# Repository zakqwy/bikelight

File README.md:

## bikelight

It's a blinky red light for the back of my bike helmet.

The circuit uses an ATtiny412 to control four red LEDs, along with a Microchip MCP73831 lipo charge controller for battery management and a micro-USB jack for charging.

The circuit is designed to be milled on a single sided chunk of FR1 using a 1/64" end mill. If you use [mods](mods.cba.mit.edu), the three layer *.svg files (holes, outline, and traces) are in the /pcb directory. After assembling and programming with [pyupdi](https://github.com/mraardvark/pyupdi) and an FTDI cable, I masked off the USB jack and slide switch and sprayed it with a few coats of clear varnish.

The pcb attaches using M3 hardware to two laser cut acetal clips, which then snap into [my helmet](https://www.bernhelmets.com/collections/bike/products/summer-watts?variant=13190223200315). If you have the same model, this will probably work for you too, otherwise you'll need to figure something else out. Laser cut files for these parts are in the /cad directory, intended to be cut from 2.5 mm acetal.

I used a 1200 mAH lipo battery since we had a few on hand; it's secured to the rear of the pcb using VHB tape. I snagged a JST PH off a spare Feather, but if you plan ahead you can buy the part [here](https://www.adafruit.com/product/1769). Note that lipo batteries are inherently dangerous, so don't build this circuit unless you're familiar with their quirks (and make sure to use one with a built-in protection circuit). Yes, if my helmet ever actually has to do its job, my head will likely catch fire.

bikelight! blink blink blink blink blink

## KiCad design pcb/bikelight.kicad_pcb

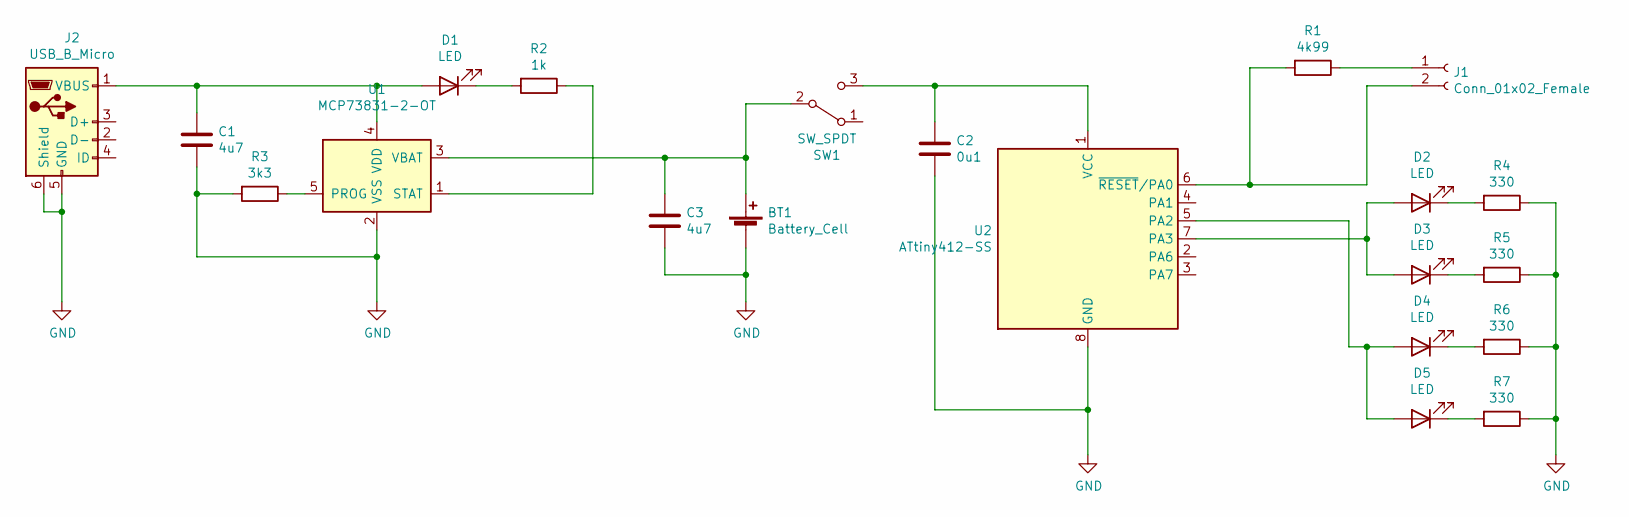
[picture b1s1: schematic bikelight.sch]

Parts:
BT1: Battery_Cell; JST_PH_S2B-PH-K_1x02_P2.00mm_Horizontal_fab
C1, C3: 4u7; fab-C1206FAB
C2: 0u1; fab-C1206FAB
D1, D2, D3, D4, D5: LED; fab-LED1206FAB
J1: Conn_01x02_Female; CONN_UPDI_2PIN
J2: USB_B_Micro; fab-USB_MICRO
R1: 4k99; fab-R1206FAB
R2: 1k; fab-R1206FAB
R3: 3k3; fab-R1206FAB
R4, R5, R6, R7: 330; fab-R1206FAB
SW1: SW_SPDT; fab-SPDTSWITCH
U1: MCP73831-2-OT; fab-SOT23-5
U2: ATtiny412-SS; SOIC-8_3.9x4.9mm_P1.27mm

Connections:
GND: BT1.2 (-), C1.2, C2.2, C3.2, J2.5 (GND), J2.6 (Shield), R3.2, R4.1, R5.1, R6.1, R7.1, U1.2 (VSS), U2.8 (GND)
unnamed: BT1.1 (+), C3.1, SW1.2 (B), U1.3 (VBAT)
unnamed: C1.1, D1.2 (A), J2.1 (VBUS), U1.4 (VDD)
unnamed: C2.1, SW1.3 (C), U2.1 (VCC)
unnamed: D1.1 (K), R2.2
unnamed: D2.1 (K), R4.2
unnamed: D2.2 (A), D3.2 (A), U2.7 (PA3)
unnamed: D3.1 (K), R5.2
unnamed: D4.1 (K), R6.2
unnamed: D4.2 (A), D5.2 (A), U2.5 (PA2)
unnamed: D5.1 (K), R7.2
unnamed: J1.1, R1.1
unnamed: J1.2, R1.2, U2.6 (~RESET~/PA0)
unnamed: R2.1, U1.1 (STAT)
unnamed: R3.1, U1.5 (PROG)

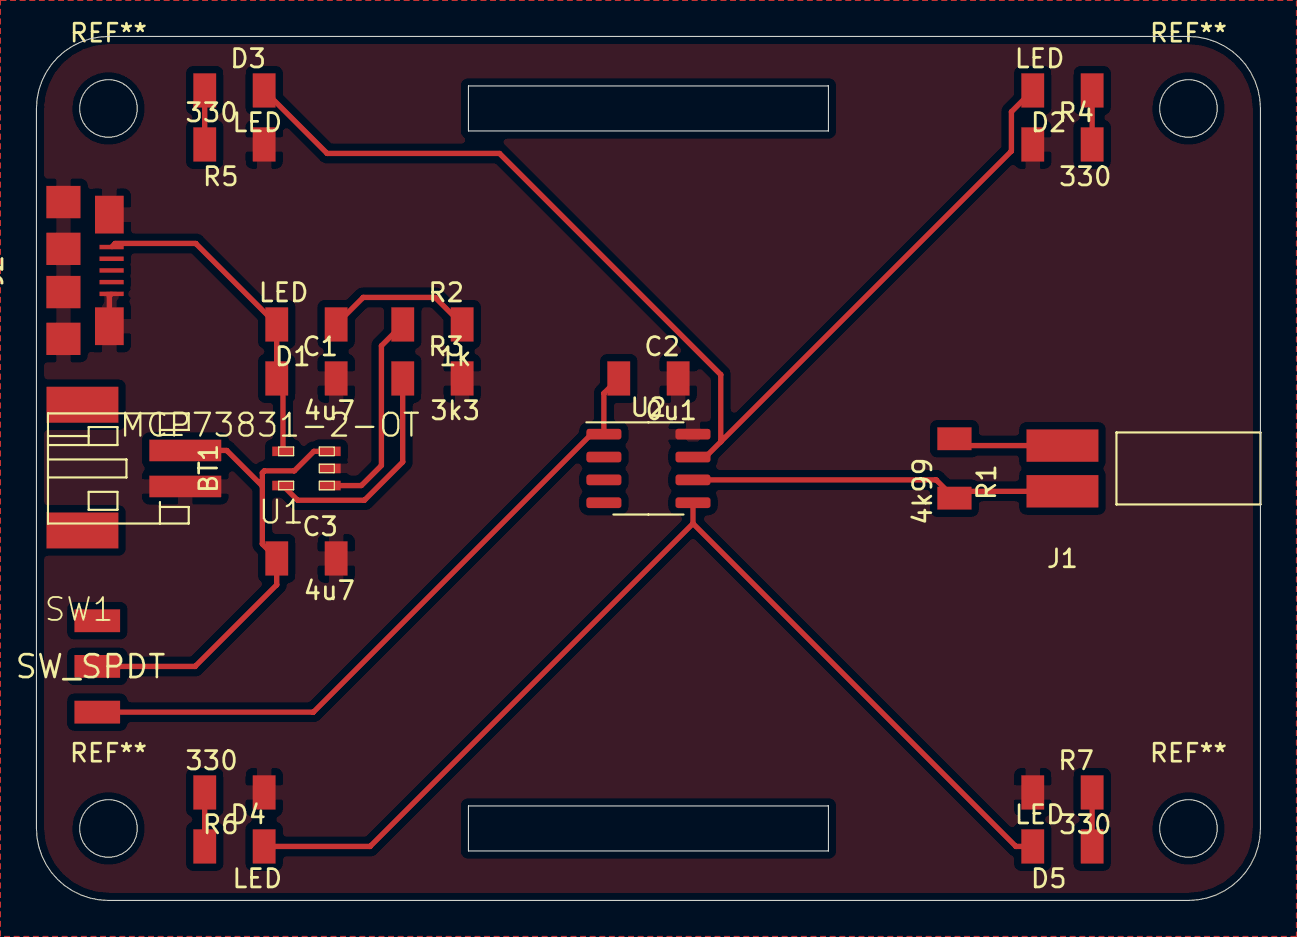
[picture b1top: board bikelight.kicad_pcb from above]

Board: 2 copper layers, 68.0 x 48.0 mm, 21 parts (0 on the bottom side), 15 nets.

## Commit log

2020-09-26 first rev
2020-09-26 doc updates
2023-05-15 added gif for markdown
